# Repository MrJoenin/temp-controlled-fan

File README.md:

# temp-controlled-fan

## Overview
This circuit uses the LM393 comparator to compare the voltage from an NTC thermister temperature sensor with a user-defined threshold. When the temperature measured by the NTC thermister exceeds the set threshold, a signal is sent to the NMOSFET, activating it, which in turn turns on an LED to indicate that the DC motor is running. Additionally, the 

## Features
- Duel Comparator (lm393) x1
- Zener Diode x1
- Temperature Sensor (NTC Thermister) x1
- LED x1
- DC Motor x1
- N Mosfet x1
- Resistors x8
- Potentiometer x1

## Software Used
- KICAD
- Multisim
- ThinkerCAD

## Files
- `circuit photos` – circuit diagrams
- `PCB files` - Gerber files, BOM etc.

## Link
- https://www.tinkercad.com/things/4xYCQ1ZHnzD-smart-temperature-controlled-fan-system

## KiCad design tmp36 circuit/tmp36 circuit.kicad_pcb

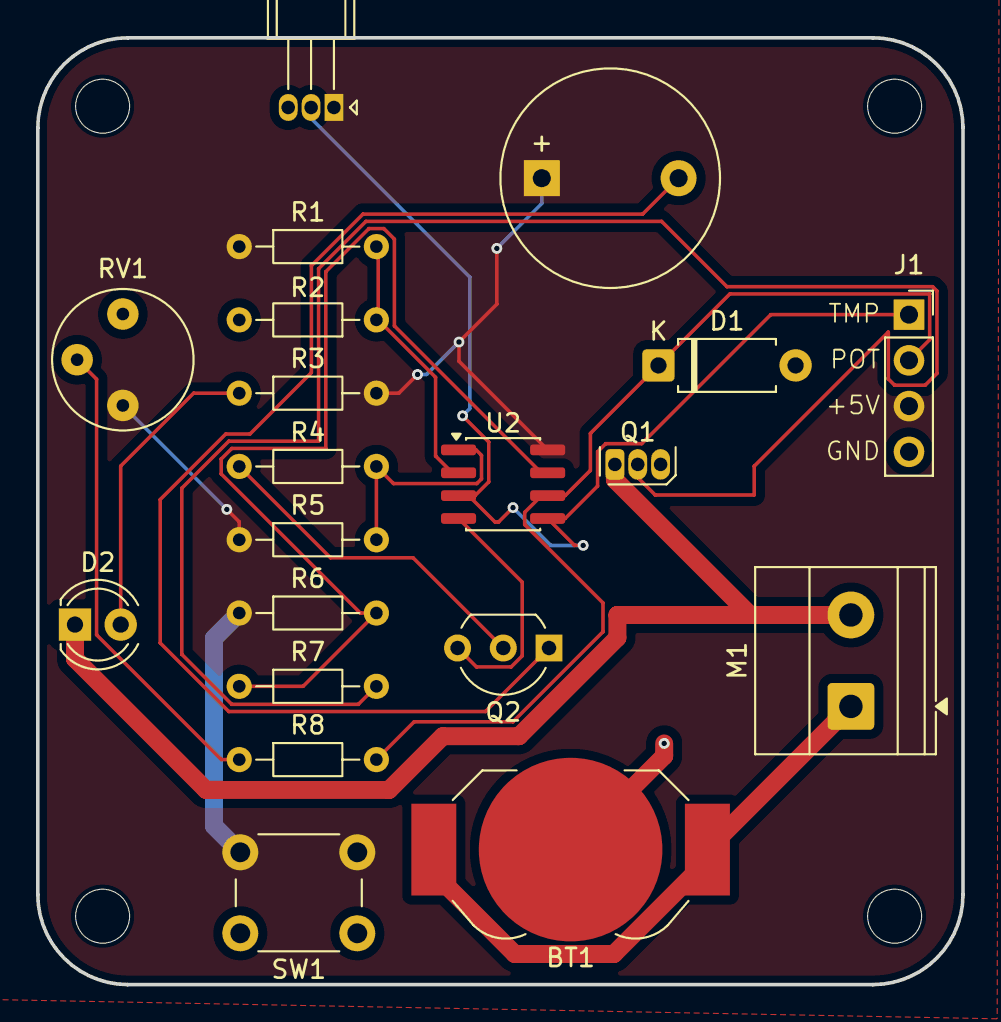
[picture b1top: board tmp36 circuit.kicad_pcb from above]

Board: 2 copper layers, 51.4 x 52.6 mm, 24 parts (0 on the bottom side), 14 nets.

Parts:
BT1: Battery_Cell; BatteryHolder_LINX_BAT-HLD-012-SMT
BZ1: Buzzer; MagneticBuzzer_StarMicronics_TMB
D1: D_Zener; D_A-405_P7.62mm_Horizontal
D2: LED; LED_D4.0mm
H1, H2, H3, H4: MountingHole; MountingHole_3mm
J1: Conn_01x04_Pin; PinSocket_1x04_P2.54mm_Vertical
M1: Motor_DC; TerminalBlock_Phoenix_MKDS-1,5-2-5.08_1x02_P5.08mm_Horizont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
Q1: NMOS; TO-92S
Q2: NPN; TO-92_Inline_Wide
Q3: NPN; TO-92_Inline_W4.0mm_Horizontal_FlatSideDown
R1: 5k; R_Axial_DIN0204_L3.6mm_D1.6mm_P7.62mm_Horizontal
R2, R6: 2k; R_Axial_DIN0204_L3.6mm_D1.6mm_P7.62mm_Horizontal
R3, R4, R5, R8: 1k; R_Axial_DIN0204_L3.6mm_D1.6mm_P7.62mm_Horizontal
R7: 10k; R_Axial_DIN0204_L3.6mm_D1.6mm_P7.62mm_Horizontal
RV1: 1k; Potentiometer_Bourns_3339P_Vertical_HandSoldering
SW1: SW_SPDT; SW_PUSH_6mm_H5mm
U2: LM393; SOIC-8_3.9x4.9mm_P1.27mm

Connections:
1out: R4.1, R5.2, U2.1
2out: R6.2, R7.1, U2.7
+5V: BZ1.1 (+), J1.3, Q3.1 (C), R1.1, R3.2, R5.1, R6.1, RV1.1, SW1.2 (B), U2.8 (V+)
GND: BT1.2 (-), D1.2 (A), J1.4, Q1.3 (S), Q2.3 (E), Q3.3 (E), R2.2, RV1.3, U2.4 (V-)
unnamed: BZ1.2 (-), Q2.1 (C)
unnamed: D2.2 (A), R3.1
unnamed: D2.1 (K), M1.2 (-), Q1.1 (D)
unnamed: Q1.2 (G), R7.2
unnamed: Q2.2 (B), R4.2
unnamed: R8.1, RV1.2
Vmot: BT1.1 (+), M1.1 (+)
pot_out: D1.1 (K), J1.2, R8.2, U2.6 (-)
tmp36_out: J1.1, Q3.2 (B), U2.3 (+), U2.5 (+)
vdr: R1.2, R2.1, U2.2 (-)

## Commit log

2025-07-21 Create PCB Files
2025-12-25 Update software used section to include KICAD
2026-06-01 Replace TMP36 with NTC thermistor in README
    Updated temperature sensor description and components list.
